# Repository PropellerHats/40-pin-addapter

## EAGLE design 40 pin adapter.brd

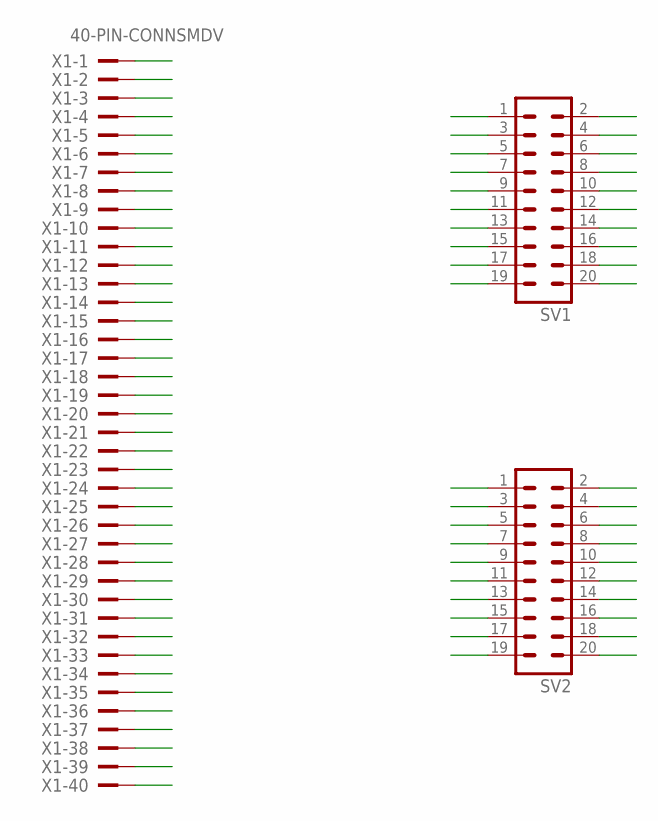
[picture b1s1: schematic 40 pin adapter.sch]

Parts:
SV1, SV2: MA10-2
X1: 40-PIN-CONNSMDV; SMD

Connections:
1: SV1.1, X1.1
2: SV1.2, X1.2
3: SV1.3, X1.3
4: SV1.4, X1.4
5: SV1.5, X1.5
6: SV1.6, X1.6
7: SV1.7, X1.7
8: SV1.8, X1.8
9: SV1.9, X1.9
10: SV1.10, X1.10
11: SV1.11, X1.11
12: SV1.12, X1.12
13: SV1.13, X1.13
14: SV1.14, X1.14
15: SV1.15, X1.15
16: SV1.16, X1.16
17: SV1.17, X1.17
18: SV1.18, X1.18
19: SV1.19, X1.19
20: SV1.20, X1.20
21: SV2.1, X1.21
22: SV2.2, X1.22
23: SV2.3, X1.23
24: SV2.4, X1.24
25: SV2.5, X1.25
26: SV2.6, X1.26
27: SV2.7, X1.27
28: SV2.8, X1.28
29: SV2.9, X1.29
30: SV2.10, X1.30
31: SV2.11, X1.31
32: SV2.12, X1.32
33: SV2.13, X1.33
34: SV2.14, X1.34
35: SV2.15, X1.35
36: SV2.16, X1.36
37: SV2.17, X1.37
38: SV2.18, X1.38
39: SV2.19, X1.39
40: SV2.20, X1.40

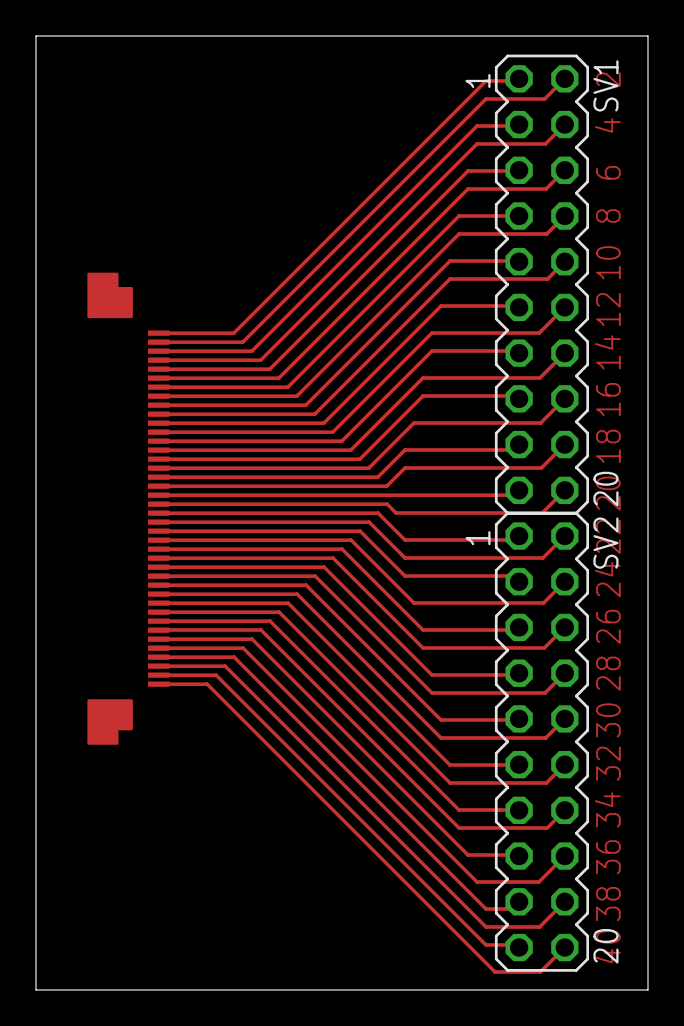
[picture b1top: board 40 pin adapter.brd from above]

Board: 2 copper layers, 34.0 x 53.0 mm, 3 parts (0 on the bottom side), 40 nets.
